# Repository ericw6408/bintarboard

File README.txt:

README.txt

Hi!
This is my Capstone project for my high school class! I have built a custom mechanical keyboard from scratch, from prototyping the pcb to designing the case, to building QMK, as well as assembling it together. 

This is my first time doing anything similar to this! YAHOOO

Current:
Soldered PCB, printed case and plate, and assembled.
Unfortunately, RDP protection was enabled, which means that flashing code onto the STM32 processor isn't possible. 

General overview of the project on https://youtu.be/W4MYoR_t5gU

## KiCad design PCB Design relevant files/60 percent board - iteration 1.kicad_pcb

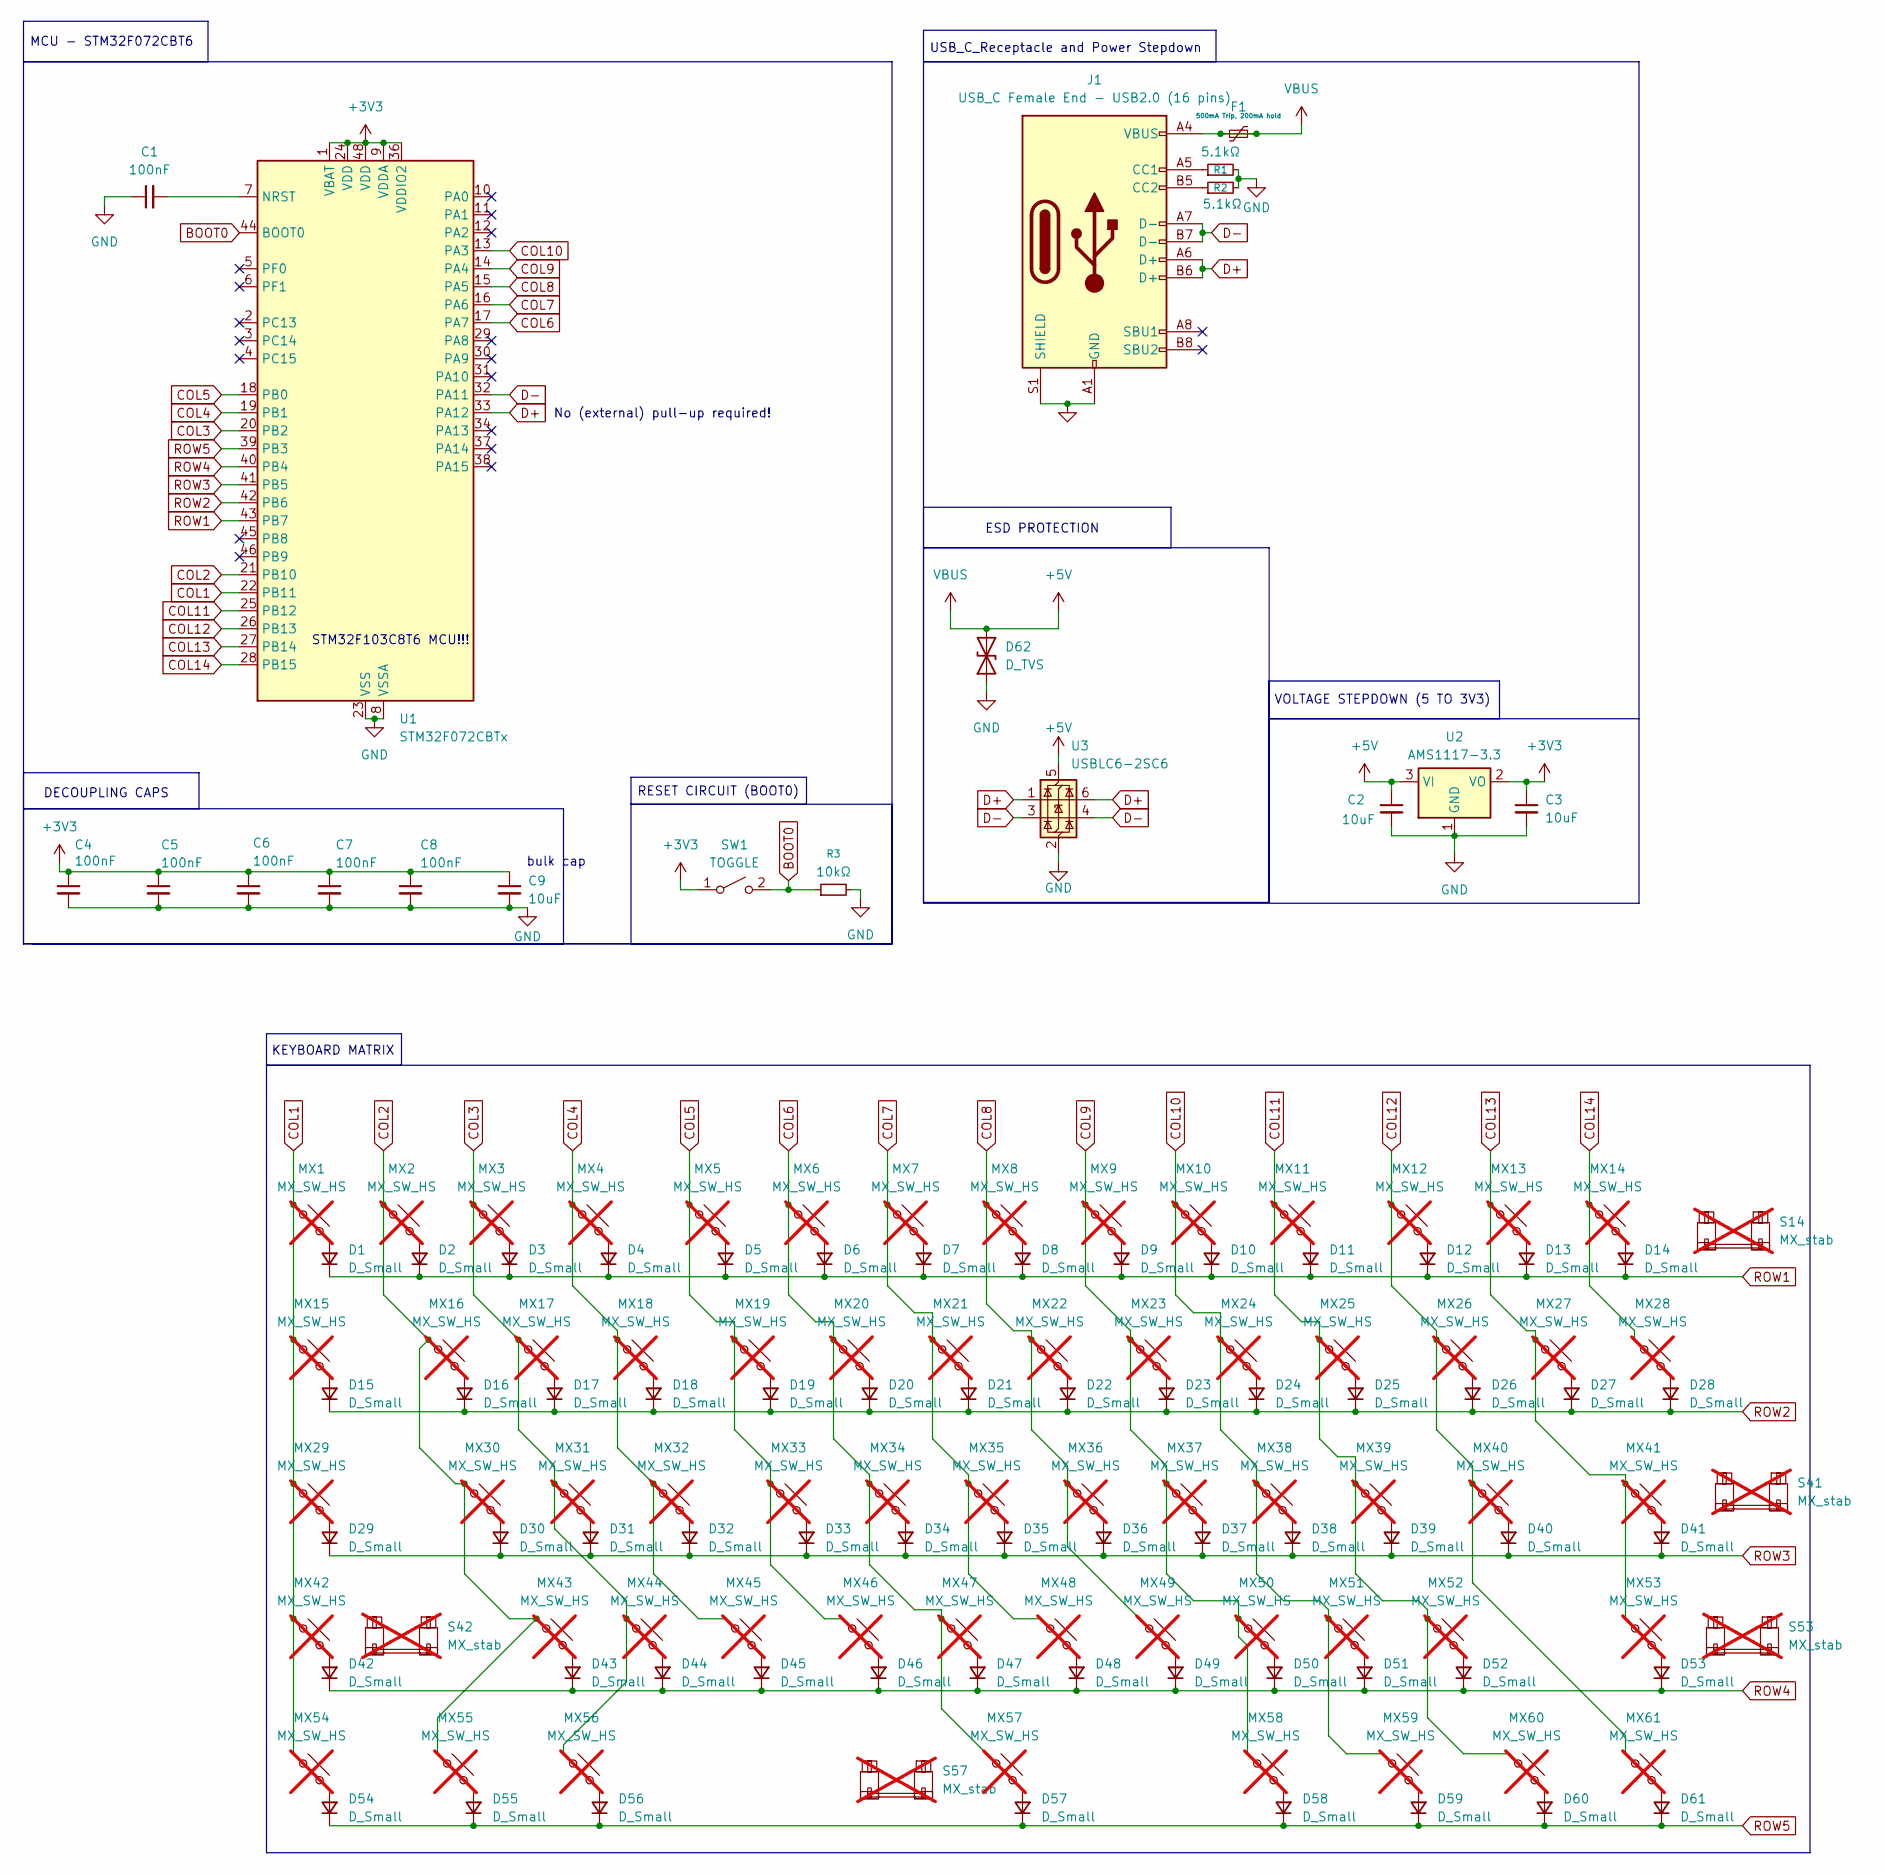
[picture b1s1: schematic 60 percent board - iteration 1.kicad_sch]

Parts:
C1, C4, C5, C6, C7, C8: 100nF; C_0402_1005Metric
C2, C3, C9: 10uF; C_1206_3216Metric
D1, D2, D3, D4, D5, D6, D7, D8, D9, D10, D11, D12, D13, D14, D15, D16, D17, D18, D19, D20, D21, D22, D23, D24, D25, D26, D27, D28, D29, D30, D31, D32, D33, D34, D35, D36, D37, D38, D39, D40, D41, D42, D43, D44, D45, D46, D47, D48, D49, D50, D51, D52, D53, D54, D55, D56, D57, D58, D59, D60, D61: D_Small; D_SOD-323
D62: D_TVS; D_SMB
F1: 500mA Trip, 200mA hold; Fuse_0402_1005Metric
J1: USB_C Female End - USB2.0 (16 pins); USB_C_Receptacle_GCT_USB4105-xx-A_16P_TopMnt_Horizontal
MX1, MX2, MX3, MX4, MX5, MX6, MX7, MX8, MX9, MX10, MX11, MX12, MX13, MX16, MX17, MX18, MX19, MX20, MX21, MX22, MX23, MX24, MX25, MX26, MX27, MX30, MX31, MX32, MX33, MX34, MX35, MX36, MX37, MX38, MX39, MX40, MX43, MX44, MX45, MX46, MX47, MX48, MX49, MX50, MX51, MX52: MX_SW_HS; SW_Hotswap_Kailh_MX_1.00u; not fitted
MX14: MX_SW_HS; SW_Hotswap_Kailh_MX_2.00u; not fitted
MX15, MX28: MX_SW_HS; SW_Hotswap_Kailh_MX_1.50u; not fitted
MX29: MX_SW_HS; SW_Hotswap_Kailh_MX_1.75u; not fitted
MX41, MX42: MX_SW_HS; SW_Hotswap_Kailh_MX_2.25u; not fitted
MX53: MX_SW_HS; SW_Hotswap_Kailh_MX_2.75u; not fitted
MX54, MX55, MX56, MX58, MX59, MX60, MX61: MX_SW_HS; SW_Hotswap_Kailh_MX_1.25u; not fitted
MX57: MX_SW_HS; SW_Hotswap_Kailh_MX_6.25u; not fitted
R1, R2: 5.1kΩ; R_0603_1608Metric
R3: 10kΩ; R_0805_2012Metric
S14, S41, S42, S53: MX_stab; STAB_MX_P_2u; not fitted
S57: MX_stab; STAB_MX_P_6.25u; not fitted
SW1: TOGGLE; SW_Push_1P1T_XKB_TS-1187A
U1: STM32F072CBTx; LQFP-48_7x7mm_P0.5mm
U2: AMS1117-3.3; SOT-223-3_TabPin2
U3: USBLC6-2SC6; SOT-23-6

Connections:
+3V3: C3.1, C4.1, C5.1, C6.1, C7.1, C8.1, C9.1, SW1.1 (A), U1.1 (VBAT), U1.9 (VDDA), U1.24 (VDD), U1.36 (VDDIO2), U1.48 (VDD), U2.2 (VO)
+5V: C2.1, D62.2 (A2), F1.1, F1.2, J1.A4 (VBUS), J1.A9 (VBUS), J1.B4 (VBUS), J1.B9 (VBUS), U2.3 (VI), U3.5 (VBUS)
BOOT0: R3.1, SW1.2 (B), U1.44 (BOOT0)
COL1: MX1.1, MX15.1, MX29.1, MX42.1, MX54.1, U1.22 (PB11)
COL2: MX2.1, MX16.1, MX30.1, MX43.1, MX55.1, U1.21 (PB10)
COL3: MX3.1, MX17.1, MX31.1, MX44.1, MX56.1, U1.20 (PB2)
COL4: MX4.1, MX18.1, MX32.1, MX45.1, U1.19 (PB1)
COL5: MX5.1, MX19.1, MX33.1, MX46.1, U1.18 (PB0)
COL6: MX6.1, MX20.1, MX34.1, MX47.1, MX57.1, U1.17 (PA7)
COL7: MX7.1, MX21.1, MX35.1, MX48.1, U1.16 (PA6)
COL8: MX8.1, MX22.1, MX36.1, MX49.1, U1.15 (PA5)
COL9: MX9.1, MX23.1, MX37.1, MX50.1, MX58.1, U1.14 (PA4)
COL10: MX10.1, MX24.1, MX38.1, MX51.1, MX59.1, U1.13 (PA3)
COL11: MX11.1, MX25.1, MX39.1, MX52.1, MX60.1, U1.25 (PB12)
COL12: MX12.1, MX26.1, MX40.1, MX61.1, U1.26 (PB13)
COL13: MX13.1, MX27.1, MX41.1, MX53.1, U1.27 (PB14)
COL14: MX14.1, MX28.1, U1.28 (PB15)
D+: J1.A6 (D+), J1.B6 (D+), U1.33 (PA12), U3.1 (I/O1), U3.6 (I/O1)
D-: J1.A7 (D-), J1.B7 (D-), U1.32 (PA11), U3.3 (I/O2), U3.4 (I/O2)
GND: C1.1, C2.2, C3.2, C4.2, C5.2, C6.2, C7.2, C8.2, C9.2, D62.1 (A1), J1.A1 (GND), J1.A12 (GND), J1.B1 (GND), J1.B12 (GND), J1.S1 (SHIELD), R1.2, R2.2, R3.2, U1.8 (VSSA), U1.23 (VSS), U1.35 (VSS), U1.47 (VSS), U2.1 (GND), U3.2 (GND)
unnamed: D1.2 (A), MX1.2
unnamed: D2.2 (A), MX2.2
unnamed: D3.2 (A), MX3.2
unnamed: D4.2 (A), MX4.2
unnamed: D5.2 (A), MX5.2
unnamed: D6.2 (A), MX6.2
unnamed: D7.2 (A), MX7.2
unnamed: D8.2 (A), MX8.2
unnamed: D9.2 (A), MX9.2
unnamed: D10.2 (A), MX10.2
unnamed: D11.2 (A), MX11.2
unnamed: D12.2 (A), MX12.2
unnamed: D13.2 (A), MX13.2
unnamed: D14.2 (A), MX14.2
unnamed: D15.2 (A), MX15.2
unnamed: D16.2 (A), MX16.2
unnamed: D17.2 (A), MX17.2
unnamed: D18.2 (A), MX18.2
unnamed: D19.2 (A), MX19.2
unnamed: D20.2 (A), MX20.2
unnamed: D21.2 (A), MX21.2
unnamed: D22.2 (A), MX22.2
unnamed: D23.2 (A), MX23.2
unnamed: D24.2 (A), MX24.2
unnamed: D25.2 (A), MX25.2
unnamed: D26.2 (A), MX26.2
unnamed: D27.2 (A), MX27.2
unnamed: D28.2 (A), MX28.2
unnamed: D29.2 (A), MX29.2
unnamed: D30.2 (A), MX30.2
unnamed: D31.2 (A), MX31.2
unnamed: D32.2 (A), MX32.2
unnamed: D33.2 (A), MX33.2
unnamed: D34.2 (A), MX34.2
unnamed: D35.2 (A), MX35.2
unnamed: D36.2 (A), MX36.2
unnamed: D37.2 (A), MX37.2
unnamed: D38.2 (A), MX38.2
unnamed: D39.2 (A), MX39.2
unnamed: D40.2 (A), MX40.2
unnamed: D41.2 (A), MX41.2
unnamed: D42.2 (A), MX42.2
unnamed: D43.2 (A), MX43.2
unnamed: D44.2 (A), MX44.2
unnamed: D45.2 (A), MX45.2
unnamed: D46.2 (A), MX46.2
unnamed: D47.2 (A), MX47.2
unnamed: D48.2 (A), MX48.2
unnamed: D49.2 (A), MX49.2
unnamed: D50.2 (A), MX50.2
unnamed: D51.2 (A), MX51.2
unnamed: D52.2 (A), MX52.2
unnamed: D53.2 (A), MX53.2
unnamed: D54.2 (A), MX54.2
unnamed: D55.2 (A), MX55.2
unnamed: D56.2 (A), MX56.2
unnamed: D57.2 (A), MX57.2
unnamed: D58.2 (A), MX58.2
unnamed: D59.2 (A), MX59.2
unnamed: D60.2 (A), MX60.2
unnamed: D61.2 (A), MX61.2
unnamed: J1.A5 (CC1), R1.1
unnamed: J1.B5 (CC2), R2.1
unnamed: C1.2, U1.7 (NRST)
ROW1: D1.1 (K), D2.1 (K), D3.1 (K), D4.1 (K), D5.1 (K), D6.1 (K), D7.1 (K), D8.1 (K), D9.1 (K), D10.1 (K), D11.1 (K), D12.1 (K), D13.1 (K), D14.1 (K), U1.43 (PB7)
ROW2: D15.1 (K), D16.1 (K), D17.1 (K), D18.1 (K), D19.1 (K), D20.1 (K), D21.1 (K), D22.1 (K), D23.1 (K), D24.1 (K), D25.1 (K), D26.1 (K), D27.1 (K), D28.1 (K), U1.42 (PB6)
ROW3: D29.1 (K), D30.1 (K), D31.1 (K), D32.1 (K), D33.1 (K), D34.1 (K), D35.1 (K), D36.1 (K), D37.1 (K), D38.1 (K), D39.1 (K), D40.1 (K), D41.1 (K), U1.41 (PB5)
ROW4: D42.1 (K), D43.1 (K), D44.1 (K), D45.1 (K), D46.1 (K), D47.1 (K), D48.1 (K), D49.1 (K), D50.1 (K), D51.1 (K), D52.1 (K), D53.1 (K), U1.40 (PB4)
ROW5: D54.1 (K), D55.1 (K), D56.1 (K), D57.1 (K), D58.1 (K), D59.1 (K), D60.1 (K), D61.1 (K), U1.39 (PB3)

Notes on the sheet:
USB_C_Receptacle and Power Stepdown
DECOUPLING CAPS
KEYBOARD MATRIX
MCU - STM32F072CBT6
bulk cap
VOLTAGE STEPDOWN (5 TO 3V3)
STM32F103C8T6 MCU!!!
No (external) pull-up required!
ESD PROTECTION
RESET CIRCUIT (BOOT0)

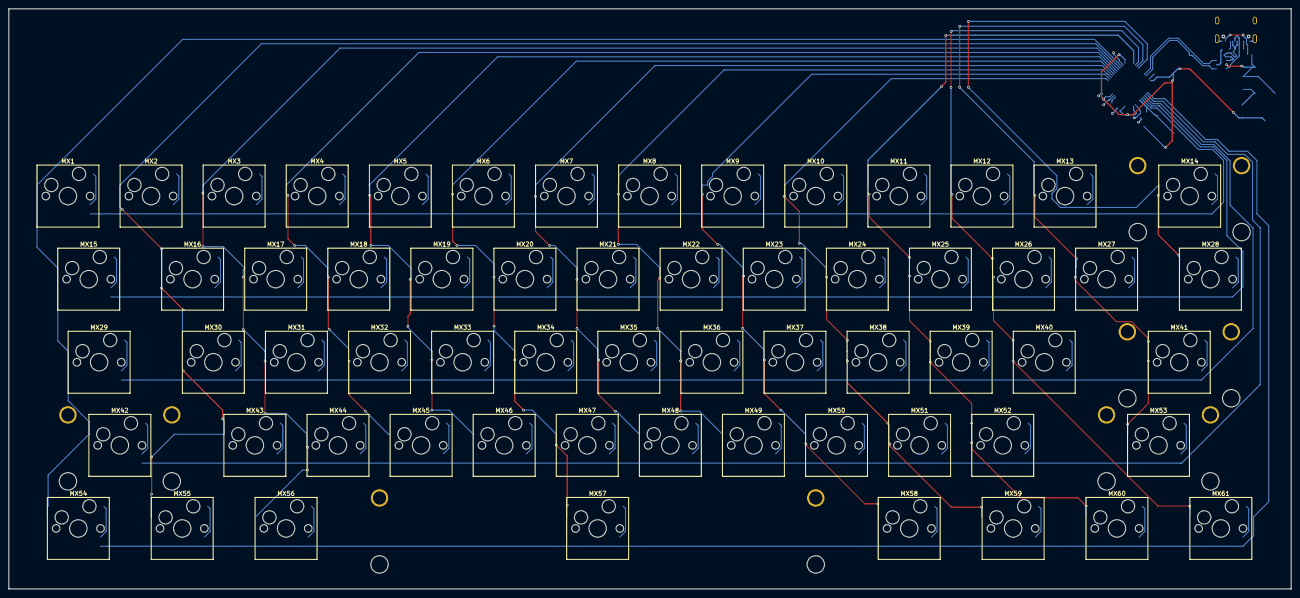
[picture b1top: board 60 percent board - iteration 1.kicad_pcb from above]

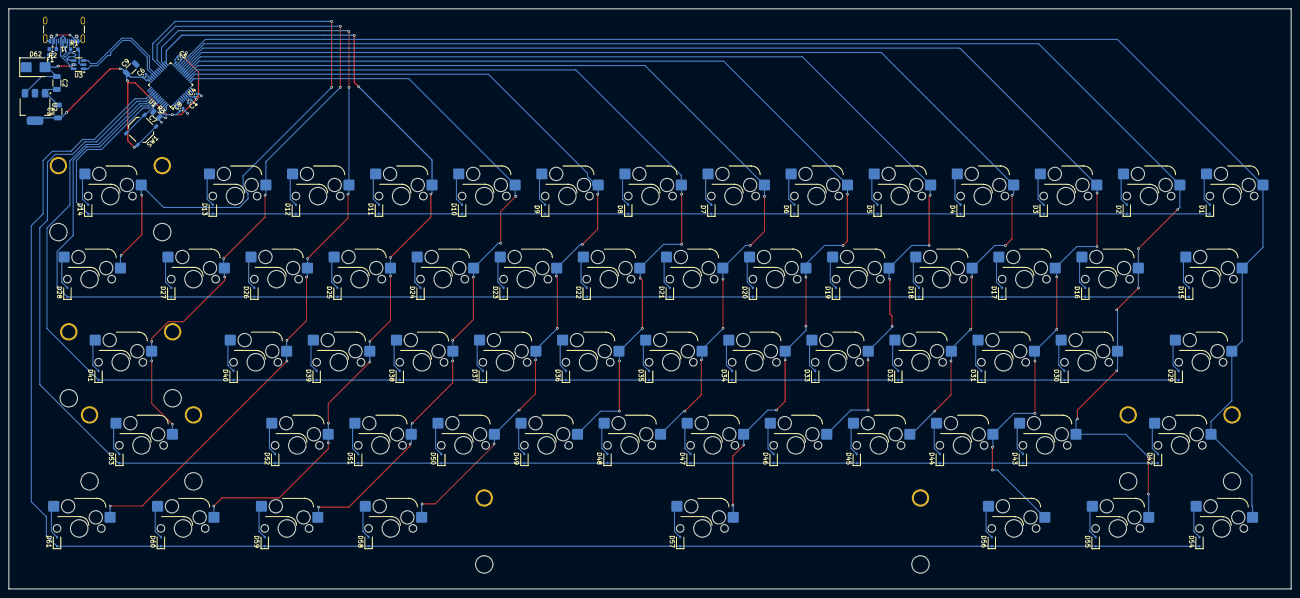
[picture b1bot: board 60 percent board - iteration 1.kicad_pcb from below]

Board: 2 copper layers, 294.0 x 133.0 mm, 146 parts (80 on the bottom side), 89 nets.

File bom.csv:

Designator,Footprint,Quantity,Value,LCSC Part #
"C1, C4, C5, C6, C7, C8",0402,6,100nF,C1525
"C2, C3, C9",1206,3,10uF,C7171
"D1, D10, D11, D12, D13, D14, D15, D16, D17, D18, D19, D2, D20, D21, D22, D23, D24, D25, D26, D27, D28, D29, D3, D30, D31, D32, D33, D34, D35, D36, D37, D38, D39, D4, D40, D41, D42, D43, D44, D45, D46, D47, D48, D49, D5, D50, D51, D52, D53, D54, D55, D56, D57, D58, D59, D6, D60, D61, D7, D8, D9",D_SOD-323,61,D_Small,C2128
D62,D_SMB,1,D_TVS,C78395
F1,0402,1,"500mA Trip, 200mA hold",C914085
J1,USB_C_Receptacle_GCT_USB4105-xx-A_16P_TopMnt_Horizontal,1,USB_C Female End - USB2.0 (16 pins),C22383818
"R1, R2",0603,2,5.1kΩ,C23186
R3,0805,1,10kΩ,C17414
SW1,SW_Push_1P1T_XKB_TS-1187A,1,TOGGLE,C318884
U1,LQFP-48_7x7mm_P0.5mm,1,STM32F072CBTx,C81720
U2,SOT-223-3_TabPin2,1,AMS1117-3.3,C6186
U3,SOT-23-6,1,USBLC6-2SC6,C7519

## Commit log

2025-02-11 readme + bill of materials beginning
2025-08-29 initial commit (basically)
2025-09-06 Gerbers, schematic & PCB files for kicad.
2025-09-06 Deleted outdated directories
2025-09-11 Case & Plate 3d design files, with tolerances.
    Thanks to my friend for printing this for me! The standoffs were weird.
2025-09-11 demo photos
2025-09-11 rev1 qmk firmware
    2 additional layers
2025-09-11 deleted old revision of qmk firmwar
2025-09-11 Latest revision version of QMK firmware
    heavily reliant on chatgpt tbh
2025-10-27 Updated readme.md
    Wrote about how the keyboard failed, and also uploaded the video link in the readme.
2025-10-27 Final image of assembled keyboard.
    THE FREAKING KEYBOARD DOESNT WOOORK :(( (but im proud of it anyway)
